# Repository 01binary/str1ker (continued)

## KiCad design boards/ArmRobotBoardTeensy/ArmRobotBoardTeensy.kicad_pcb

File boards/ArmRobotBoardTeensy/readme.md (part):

# Arm Motor Control Board

## Hardware

A Teensy 4.0-based board that controls one 3-degree of freedom (DoF) robot arm with three motors and an end-effector solenoid.

+ The first joint has a digital absolute encoder (AS5045 on SPI bus, see the [custom encoder board](../ArmEncoderBoard/)) and a relative encoder (A/B quadrature interrupt pins), in addition to two limit switches that automatically cut off the "enabled" signal for the first [Mini IBT](https://www.amazon.com/L6201P-Module-H-Bridge-Control-12V-48V/dp/B09N7L9TLB) motor driver.
+ The other two joints have potentiometers and linear actuators with built-in limit switches connected to the remaining two [Mini IBT](https://www.amazon.com/L6201P-Module-H-Bridge-Control-12V-48V/dp/B09N7L9TLB) motor drivers.
+ All three motor drivers have red *enabled* LEDs and blue *activity* LEDs.
+ The solenoid has a blue *activity* LED that indicates when the signal is being sent to [Adafruit MOSFET Driver](https://www.adafruit.com/product/5648).
+ The SPI connection for the absolute encoder has a red *status* LED.
+ [Adafruit INA260](https://www.adafruit.com/product/4226) Voltage and current sensor is attached to the I2C bus. This is used for system identification and PID controller tuning in the lab (not used in production).

The motor drivers control the following motors and actuators:

|Joint|Description|Motor|
|-|-|-|
|Base|Rotates the arm|[DumaDynamics 56RPM Right Angle Gear Motor w/ 13PPR](https://www.robotshop.com/products/duma-dynamics-56rpm-right-angle-gear-motor-w-13ppr-hall-sensor-encoder)
|Shoulder|Raises or lowers the arm|[Firgelli Classic Rod Linear Actuator](https://www.firgelliauto.com/products/linear-actuators?variant=843909131)
|Elbow|Extends or contracts the arm|[Firgelli Bullet Mini Actuator](https://www.firgelliauto.com/products/bullet-series-mini-actuators?variant=20791982342)

The potentiometers that measure shoulder and elbow joint positions are [NP24HS Series](https://p3america.com/np24hs-series/) from P3 America.

## Software

### Controller

+ All three actuators are PID controlled, with encoders normalized to the travel range.
+ Teensy is configured for 12-bit analog conversion.
+ The PID constants for all three actuators are adjustable via [ROS parameters](../../config/arm.yaml) loaded for the ROS Serial node running on the Teensy 4.0 MCU soldered onto this board.

### ROS Interface

+ Target (set-point) positions for all three joints are subscribed to a ROS queue.
+ Velocities of all three joints are subscribed to a ROS queue (velocity overrides position).
+ Trajectory for the whole arm is subscribed to ROS queue (MoveIt Integration with positions, velocities, and torques).
+ Absolute positions of all three joints are published to ROS queue.
+ Status for encoder, motor drivers, voltage, and current are published to ROS queue with lesser frequency.

## Pin Mapping

This board is essentially a shield, exposing convenient, labeled locking connectors for all of the devices, and indicating PWM enabled/activity with LEDs.

|Pin              |Net        |Description
|-----------------|-----------|-------------------
|3V3              |`+3.3V`    |Power
|GND              |`GND`      |Ground
|SPI CS   (`D10`) |`CS`       |Absolute Encoder CS
|SPI SCK  (`D13`) |`SCK`      |Absolute Encoder CK
|SPI MISO (`D12`) |`MISO`     |Absolute Encoder DO
|`D9`             |`SPIS  `   |Absolute Encoder Status LED
|I2C SCL (`D19`)  |`SCL`      |Voltage/Current Sensor SCL
|I2C SDA (`D18`)  |`SDA`      |Voltage/Current Sensor SDA
|`D2`             |`A`        |Quadrature Encoder A
|`D5`             |`B`        |Quadrature Encoder B
|`A0` (`D14`)     |`A0`       |Potentiometer 1
|`A1` (`D15`)     |`A1`       |Potentiometer 2
|`D16`            |`PWM1VT`   |Motor Driver 1 Current Sense
|`D0`             |`PWM1ENSIG`|Motor Driver 1 Enabled
|`D1`             |`RPWM1`    |Motor Driver 1 RPWM
|`D3`             |`LPWM1`    |Motor Driver 1 LPWM
|`D4`             |`PWM2VT`   |Motor Driver 2 Current Sense
|`D6`             |`PWM2EN`   |Motor Driver 2 Enabled
|`D7`             |`RPWM2`    |Motor Driver 2 RPWM
|`D8`             |`LPWM2`    |Motor Driver 2 LPWM
|`D20`            |`PWM3VT`   |Motor Driver 3 Current Sense
|`D21`            |`PWM3EN`   |Motor Driver 3 Enabled
|`D22`            |`RPWM3`    |Motor Driver 3 RPWM
|`D23`            |`LPWM3`    |Motor Driver 3 LPWM
|`D17`            |`SIG`      |Solenoid Driver Signal

## Motor Drivers

There are three external [Mini IBT](https://www.amazon.com/L6201P-Module-H-Bridge-Control-12V-48V/dp/B09N7L9TLB) motor drivers, each with `EN` (enabled), `RPWM` (right PWM velocity), `LPWM` (left PWM velocity) and `VT` (current sense) pins.

Each motor driver has a *status LED* that lights up whenever the driver is enabled (`EN` is `HIGH`).

Each motor driver also has two *activity LEDs* that blink whenever `RPWM` or `LPWM` pins are active. Logic *AND* gates are used along with a 555 timer to blink these activity LEDs whenever a non-zero PWM signal is being sent to these pins.

The 555 timer is configured with two resistors, `10K` and `360K`, for a blink rate of `~2 Hz` (two blinks per second).

The first PWM channel has two normally-open limit switches that cut off the `EN` signal from microcontroller when closed by using a transistor. In this way, even if this PWM channel is enabled by the controller, closing either switch will disable it.

The two linear actuators that control forearm and elbow joints have built-in limit switches but the motor that rotates the arm will happily keep pushing when reaching the limits of its motion, which damages the hardware unnecessarily - these external limit switches solve that problem.

Each motor driver also has a *current sense* pin. These are connected to Teensy ADC pins to read the current of each motor, which is accomplished by placing a `5.1K` resistor to `GND` on current sense lines. The current can be calculated using this formula:

`I = V * 8500 / R` where

+ `I` is the motor current
+ `V` is read voltage from the ADC
+ `R` is the chosen resistor, in this case `5.1K` chosen to produce `3V` on the ADC pin at `5A` (maximum rated) motor current.

Motor drivers are labeled as follows on the schematic:

|Net         |Description
|------------|----------------------------|
|`PWM1EN`    |PWM Channel `1` Enabled
|`RPWM1`     |PWM Channel `1` RPWM
|`LPWM1`     |PWM Channel `1` LPWM
|`PWM1VT`    |PWM Channel `1` Current Sense
|`PWM2EN`    |PWM Channel `2` Enabled
|`RPWM2`     |PWM Channel `2` RPWM
|`LPWM2`     |PWM Channel `2` LPWM
|`PWM2VT`    |PWM Channel `2` Current Sense
|`PWM3EN`    |PWM Channel `3` Enabled
|`RPWM3`     |PWM Channel `3` RPWM
|`LPWM3`     |PWM Channel `3` LPWM
|`PWM3VT`    |PWM Channel `3` Current Sense

## Solenoid

There is one external solenoid connected to [Adafruit MOSFET Driver](https://www.adafruit.com/product/5648) with `VDD` (power), `GND` (ground), and `SIG` (signal) pins. The solenoid driver is enabled when it gets power from Teensy on the `VDD` pin, and gets triggered whenever `SIG` pin is `HIGH`.

The solenoid signal pin has its own activity LED which lights up whenever the solenoid is triggered through the `SIG` pin.

|Net         |Description
|------------|----------------------------|
|`SIG`       |Solenoid Trigger

## Absolute Encoder

An external [absolute encoder board](../ArmEncoderBoard/) is attached to Teensy SPI bus with pins `VDD` (power), `CS` (chip select), `SCK` (SPI clock), `MISO` (SPI input), and `GND` (ground).

When the communication with the encoder is initialized successfully, the controller will set pin `D9` to `HIGH`. This pin is connected to a red encoder status LED.

|Net         |Description
|------------|----------------------------|
|`3V3`       |Absolute Encoder Power
|`GND`       |Absolute Encoder Ground
|`SPIS`      |Absolute Encoder Status LED
|`CS`        |Absolute Encoder SPI Select
|`SCK`       |Absolute Encoder SPI Clock
|`MISO`      |Absolute Encoder SPI Output

## Relative Encoder

An external relative encoder is attached to Teensy interruptable pins `D2` and `D5`. Like the absolute encoder, it is powered through Teensy 3.3V and Ground pins.

This encoder is built into the [DumaDynamics](https://www.robotshop.com/products/duma-dynamics-56rpm-right-angle-gear-motor-w-13ppr-hall-sensor-encoder) motor used to rotate the arm.

|Net         |Description
|------------|----------------------------|
|`3V3`       |Relative Encoder Power
|`GND`       |Relative Encoder Ground
|`A`         |Relative Encoder A Channel
|`B`         |Relative Encoder B Channel

## Potentiometers

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
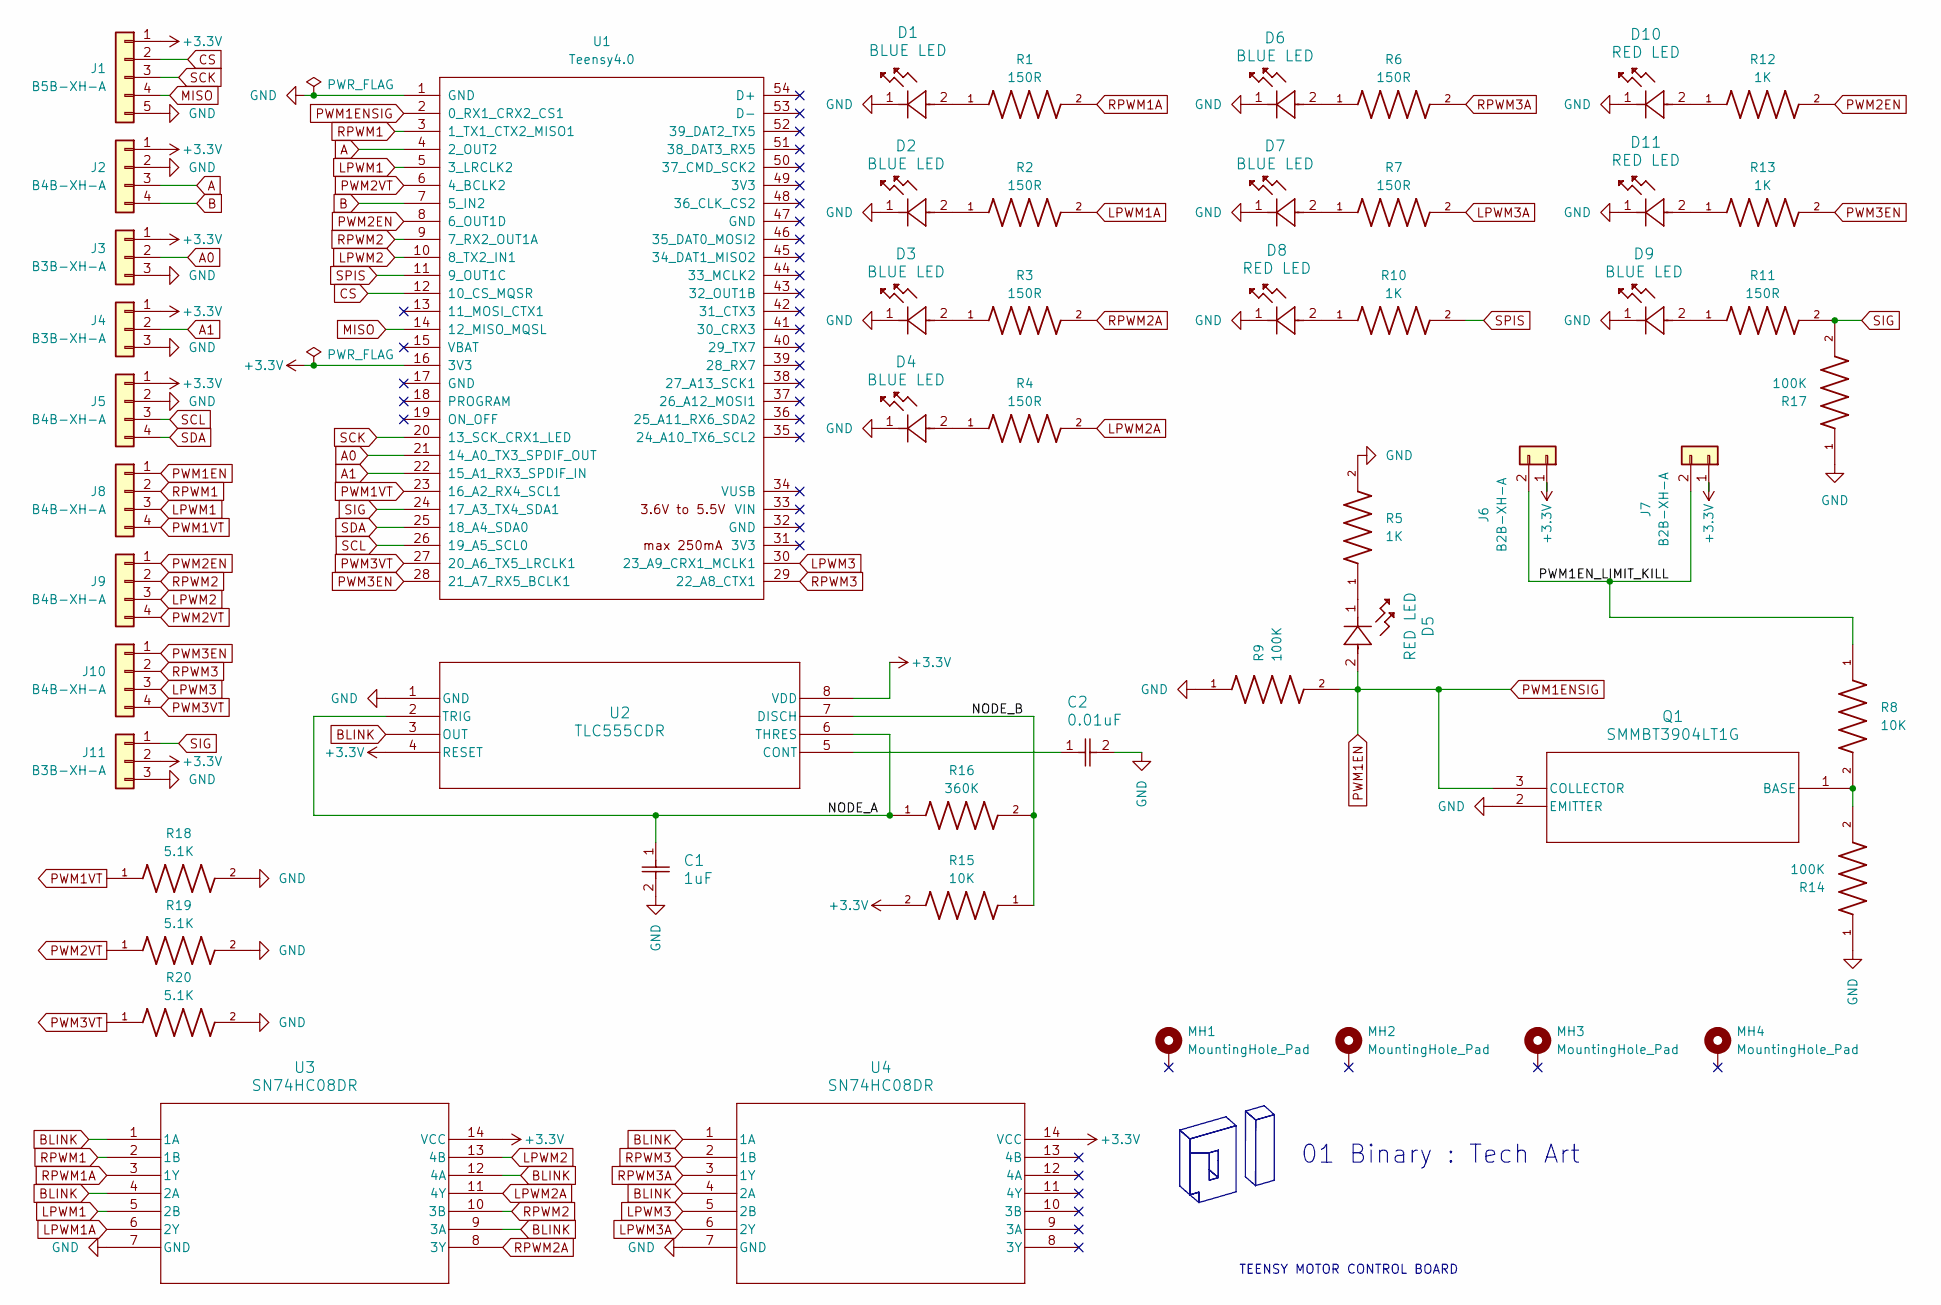
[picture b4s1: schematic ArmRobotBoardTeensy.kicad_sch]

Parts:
C1: 1uF; CC0603JRX7R7BB105; LCSC C519560
C2: 0.01uF; C0402C103J4RACTU; LCSC C2167451
D1, D2, D3, D4, D6, D7, D9: BLUE LED; 150080BS75000_Modified; LCSC C6067133
D5, D8, D10, D11: RED LED; NCD0603R1; LCSC C84263
J1: B5B-XH-A; JST_XH_B5B-XH-A_1x05_P2.50mm_Vertical
J2, J5, J8, J9, J10: B4B-XH-A; JST_XH_B4B-XH-A_1x04_P2.50mm_Vertical
J3, J4, J11: B3B-XH-A; JST_XH_B3B-XH-A_1x03_P2.50mm_Vertical
J6, J7: B2B-XH-A; JST_XH_B2B-XH-A_1x02_P2.50mm_Vertical
MH1, MH2, MH3, MH4: MountingHole_Pad; MountingHole_3.2mm_M3_ISO7380_Pad
Q1: SMMBT3904LT1G; LCSC C84555
R1, R2, R3, R4, R6, R7, R11: 150R; RCG06031K00FKEA; LCSC C114608
R5, R10, R12, R13: 1K; RCG06031K00FKEA; LCSC C4264491
R8, R15: 10K; CRCW060310K0FKEA; LCSC C844918
R9, R14, R17: 100K; CRCW0603100KFKEA; LCSC C844916
R16: 360K; RC0603FR-07360KL; LCSC C137740
R18, R19, R20: 5.1K; RC0603FR-075K1L; LCSC C105580
U1: Teensy4.0; Teensy40_SMT
U2: TLC555CDR; LCSC C6986
U3, U4: SN74HC08DR; LCSC C337768

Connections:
+3.3V: J1.1, J2.1, J3.1, J4.1, J5.1, J6.1, J7.1, J11.2, R15.2, U1.16 (3V3), U2.4 (RESET), U2.8 (VDD), U3.14 (VCC), U4.14 (VCC)
/NODE_A: C1.1, R16.1, U2.2 (TRIG), U2.6 (THRES)
/NODE_B: R15.1, R16.2, U2.7 (DISCH)
/PWM1EN_LIMIT_KILL: J6.2, J7.2, R8.1
A: J2.3, U1.4 (2_OUT2)
A0: J3.2, U1.21 (14_A0_TX3_SPDIF_OUT)
A1: J4.2, U1.22 (15_A1_RX3_SPDIF_IN)
B: J2.4, U1.7 (5_IN2)
BLINK: U2.3 (OUT), U3.1 (1A), U3.4 (2A), U3.9 (3A), U3.12 (4A), U4.1 (1A), U4.4 (2A)
CS: J1.2, U1.12 (10_CS_MQSR)
GND: C1.2, C2.2, D1.1, D2.1, D3.1, D4.1, D6.1, D7.1, D8.1, D9.1, D10.1, D11.1, J1.5, J2.2, J3.3, J4.3, J5.2, J11.3, Q1.2 (EMITTER), R5.2, R9.1, R14.1, R17.1, R18.2, R19.2, R20.2, U1.1 (GND), U2.1 (GND), U3.7 (GND), U4.7 (GND)
LPWM1: J8.3, U1.5 (3_LRCLK2), U3.5 (2B)
LPWM1A: R2.2, U3.6 (2Y)
LPWM2: J9.3, U1.10 (8_TX2_IN1), U3.13 (4B)
LPWM2A: R4.2, U3.11 (4Y)
LPWM3: J10.3, U1.30 (23_A9_CRX1_MCLK1), U4.5 (2B)
LPWM3A: R7.2, U4.6 (2Y)
MISO: J1.4, U1.14 (12_MISO_MQSL)
unnamed: D1.2, R1.1
unnamed: D2.2, R2.1
unnamed: D3.2, R3.1
unnamed: D4.2, R4.1
unnamed: D5.1, R5.1
unnamed: D6.2, R6.1
unnamed: D7.2, R7.1
unnamed: D8.2, R10.1
unnamed: D9.2, R11.1
unnamed: D10.2, R12.1
unnamed: D11.2, R13.1
unnamed: Q1.1 (BASE), R8.2, R14.2
unnamed: C2.1, U2.5 (CONT)
PWM1EN: D5.2, J8.1, Q1.3 (COLLECTOR), R9.2, U1.2 (0_RX1_CRX2_CS1)
PWM1VT: J8.4, R18.1, U1.23 (16_A2_RX4_SCL1)
PWM2EN: J9.1, R12.2, U1.8 (6_OUT1D)
PWM2VT: J9.4, R19.1, U1.6 (4_BCLK2)
PWM3EN: J10.1, R13.2, U1.28 (21_A7_RX5_BCLK1)
PWM3VT: J10.4, R20.1, U1.27 (20_A6_TX5_LRCLK1)
RPWM1: J8.2, U1.3 (1_TX1_CTX2_MISO1), U3.2 (1B)
RPWM1A: R1.2, U3.3 (1Y)
RPWM2: J9.2, U1.9 (7_RX2_OUT1A), U3.10 (3B)
RPWM2A: R3.2, U3.8 (3Y)
RPWM3: J10.2, U1.29 (22_A8_CTX1), U4.2 (1B)
RPWM3A: R6.2, U4.3 (1Y)
SCK: J1.3, U1.20 (13_SCK_CRX1_LED)
SCL: J5.3, U1.26 (19_A5_SCL0)
SDA: J5.4, U1.25 (18_A4_SDA0)
SIG: J11.1, R11.2, R17.2, U1.24 (17_A3_TX4_SDA1)
SPIS: R10.2, U1.11 (9_OUT1C)

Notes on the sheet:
TEENSY MOTOR CONTROL BOARD
01 Binary : Tech Art

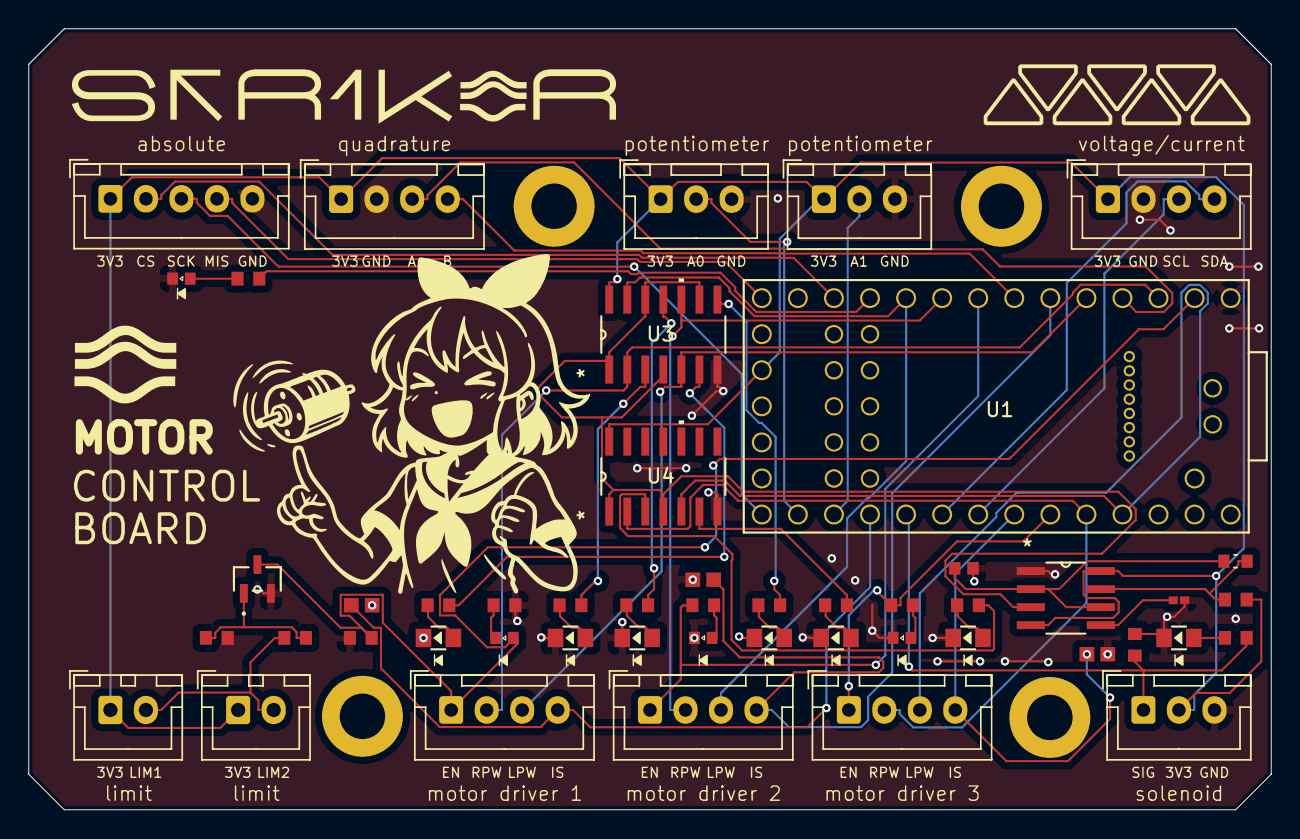
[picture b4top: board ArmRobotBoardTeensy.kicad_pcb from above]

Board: 2 copper layers, 87.5 x 55.0 mm, 53 parts (0 on the bottom side), 48 nets.

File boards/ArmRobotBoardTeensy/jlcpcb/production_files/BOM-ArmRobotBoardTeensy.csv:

Comment,Designator,Footprint,LCSC,Quantity
0.01uF,C2,C0402C103J4RACTU,C2167451,1
100K,"R14,R17,R9",CRCW0603100KFKEA,C844916,3
10K,"R15,R8",CRCW060310K0FKEA,C844918,2
150R,"R1,R11,R2,R3,R4,R6,R7",RCG06031K00FKEA,C114608,7
1uF,C1,CC0603JRX7R7BB105,C519560,1
360K,R16,RC0603FR-07360KL,C137740,1
470R,"R10,R12,R13,R5",RC0603FR-07470RL,C114669,4
BLUE LED,"D1,D2,D3,D4,D6,D7,D9",150080BS75000_Modified,C6067133,7
PINK LED,"D10,D11,D5,D8",LED_XL-2012SURC_XLG,C965812,4
SMMBT3904LT1G,Q1,SMMBT3904LT1G,C84555,1
SN74HC08DR,"U3,U4",SN74HC08DR,C337768,2
TLC555CDR,U2,TLC555CDR,C6986,1

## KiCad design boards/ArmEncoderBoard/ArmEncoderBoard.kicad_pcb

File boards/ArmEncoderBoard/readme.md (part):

# Arm Encoder Board

A custom board that simplifies mounting `AS5045` hall-effect on-axis encoder with 12-bit resolution onto robot joints.

> Ready-made alternatives like [AS5045 Adapter Board](https://www.digikey.com/en/products/detail/ams-osram-usa-inc/as5045-adapterboard/2339623) do exist, but have extra pins not used in this project, and a footprint that makes them hard to mount.

## Power

For `3.3V` operation `VDD5V` and `VDD3V3` are bridged and routed to `VIN` (3.3V). A single `100nF` decoupling capacitor is placed at the bridge (close to the IC) to `GND`.

## Signal

The following is documented in [AS5045 specifications](./doc/AS5045Encoder.pdf):

+ Synchronous Serial Interface ([SSI](https://knowledge.ni.com/KnowledgeArticleDetails?id=kA00Z0000019MgLSAU)) with one-way communication, `MOSI` line not used
+ Compatible with SPI mode 1 (`CPOL` = `0`, `CPHA` = `1`)
+ Transfer begins when `CSn` is `LOW`
+ MSB-first, clocked data output

> The encoder continuously shifts out an 18-bit data frame containing the absolute position and flags in response to clock input without having to request this information - that's what makes its interface *SSI* instead of *SPI*.

In addition to the digital communication interface, AS5045 also exposes these pins:

+ Quadrature `A`, `B` which can take on different values (according to [grey code](https://cool-emerald.blogspot.com/2014/03/reading-rotary-encoder-using.html) specification) as the magnet angle is changing
+ Index `I`, which is signaled when the magnet passes the zero position (typically used to count complete revolutions)
+ Magnet `MagINC`, `MagDEC` pins that indicate magnetic field strength and changing of distance between sensor and magnet (can be used to troubleshoot bad readings or "wobbly" mounting where the magnet changes distance to sensor as it rotates)

## Data Format

The data frame contains 18 bits: 12 data bits, 5 status bits, and 1 parity bit.

| Bit  | Size | Name     | Description
| ---- | ---- | -------- | -------------------------------
| 0–11 | 12   | Position | Angle value (MSB first)
| 12   | 1    | OCF      | Offset Compensation Finished
| 13   | 1    | COF      | CORDIC overflow (invalid angle)
| 14   | 1    | LIN      | Linearity alarm
| 15   | 1    | MagINC   | Magnet too far
| 16   | 1    | MagDEC   | Magnet too close
| 17   | 1    | Parity   | Even parity over previous bits

In practice, it's enough to simply read the first `16` bits using [SPI.transfer16](https://docs.arduino.cc/language-reference/en/functions/communication/SPI/transfer/) function commonly available on Arduino-like microcontrollers such as Teensy.

## Indicators

LEDs are attached to quadrature and index pins as well as magnetic field status pins:

+ The `A` LED blinks when receiving quadrature input (magnet is moving)
+ The `I` LED lights when the encoder is at zero position (magnet is near zero position)
+ The `MagINC` and `MagDEC` LEDs indicate the quality of readings:

|MagINC|MagDEC|Description
|-|-|-
|`0`|`0`|Distance to magnet is not changing, magnetic field OK
|`0`|`1`|Distance to magnet is increasing
|`1`|`0`|Distance to magnet is decreasing
|`1`|`1`|Magnetic field too low (magnet too far from sensor)

The following components are used to enable this:

+ `SN74LVC2G17DBVR` two-channel Schmitt buffer
+ `BAT54WS` Schottky diodes
+ `470K` resistors (transistor base bleed)
+ `47K` resistors (transistor base resistor)
+ `100K` resistors (envelope discharge)
+ `1uF` capacitors (envelope storage)
+ `100nF` capacitor (buffer decoupling)
+ `150R` and `1K` resistors (LED current limit)
+ `MMBT3904` transistors (LED sink drivers)

The `A` quadrature signal from the encoder indicates activity and is connected in the following network:

|Signal|Pin|
|-|-|
|`A`|AS5045 `A` pin going to Schmitt buffer input
|`A_EDGE`|Cleaned edges from Schmitt buffer output
|`A_PULSE`|RC circuit that turns edges into pulses
|`A_ENV`|Envelope circuit that makes pulses last longer
|`A_BLEED`|Envelope bleed
|`A_BASE`|Transistor base input
|`BLUE_CATHODE`|Blue LED cathode
|`BLUE_ANODE`|Blue LED anode

The `I` index signal from the encoder indicates zero position and is connected in the following network:

|Signal|Pin|
|-|-|
|`I`|AS5045 `I` pin going to Schmitt buffer input
|`I_BUF`|Schmitt buffer output
|`I_ENV`|Envelope circuit that makes pulses last longer
|`I_BLEED`|Envelope bleed
|`I_BASE`|Transistor base input
|`BLUE_CATHODE`|Blue LED cathode
|`BLUE_ANODE`|Blue LED anode

### Schmitt Buffer

The Schmitt Trigger Buffer clamps quadrature signals to either `HIGH` or `LOW`, which *cleans the edges* of these signals, making them a *sharp* square wave instead of a *noisy*, approximate, square wave with *soft* edges.

This conditioning is needed because the later stages (a differentiator and an integrator) amplify, and therefore are very sensitive to, noise.

### RC Filter (Differentiator)

The differentiator, implemented by using an RC (*Resistor and Capacitor*) circuit, reacts to *changes* in voltage level.

If the input voltage changes from `HIGH` to `LOW`, the output from the differentiator is `HIGH`, same from `LOW` back to `HIGH`. The differentiator stays `LOW` when the voltage is not changing.

This makes the `A` LED light only when the quadrature signal changes. It's the only way to make an *activity* LED for this kind of signal because a quadrature channel may be left either `HIGH` or `LOW` depending on when the thing being measured stops moving (there is a truth table called the [grey code](https://cool-emerald.blogspot.com/2014/03/reading-rotary-encoder-using.html) that describes the possible states).

### Envelope Generator (Integrator)

Envelope generators modify the transient characteristics of the incoming signal. The one used here acts like an integrator (it accumulates a value over time) by making the signal rise quickly (fast attack) but decay slowly (slow release).

> Fast attack/slow release combination creates "sustain" which enables the LED indicators to stay on long enough to be seen as a "blink" by the human eye after the differentiator detects a change (movement).

Without this part of the circuit, the LEDs would strobe so fast that to a human they would look dimly lit.

### Transistors

Transistors are used to drive LEDs from the power source, using AS5045's A/I pins as on/off switches so they don't drive LEDs directly.

+ Emitter connects to `GND`
+ Collector connects to LED cathode
+ Base connects to `ENV` through `47K` base resistor
+ Base connects to `GND` through `470K` pull-down resistor
+ LED anode connects to `3.3V` through LED resistor (depending on LED color)

### Open-Drain Outputs

The `MagINC` and `MagDEC` pins on AS5045 are open-drain, active-low outputs:

+ When the signals are off (`High-Z`), `10K` resistors are used to pull the lines up to `VIN` bus voltage, making the voltage potential across the corresponding LEDs zero and turning them off (both cathode and anode are bridged to `VIN`).
+ When the signals are on (`LOW`), the LED cathodes get bridged to `GND` through these AS5045 pins (and `1K` current-limiting resistors), while LED anodes remain bridged to `VIN` as before, generating a positive voltage potential and turning the LEDs on.

## Connector

The `JST-XH` connector is designed to accomodate a 5-pin `SSI` interface:

|Position|1|2|3|4|5
|-|-|-|-|-|-|
|Signal|`3V3`|`CS`|`SCK`|`MISO`|`GND`|

This is designed for a simple 5-terminal ribbon with a JST-XH locking connector crimped on.

## Miscellaneous

The following components appear on the board other than the encoder and the connector:

+ `100nF` (`0.1uF`) to `GND` on `VDD`: decoupling capacitor
+ `VDD` and `VDD3V3` bridged on `VIN`: for 3.3V operation
+ `4.7K` to `GND` on `SCK`: clock pull-down
+ `4.7K` to `VIN` on `CS`: chip select pull-up

## Example

```c++
#define CS              10
#define MAG_INC_MASK    0x0001
#define LIN_MASK        0x0002
#define COF_MASK        0x0004
#define OCF_MASK        0x0008
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
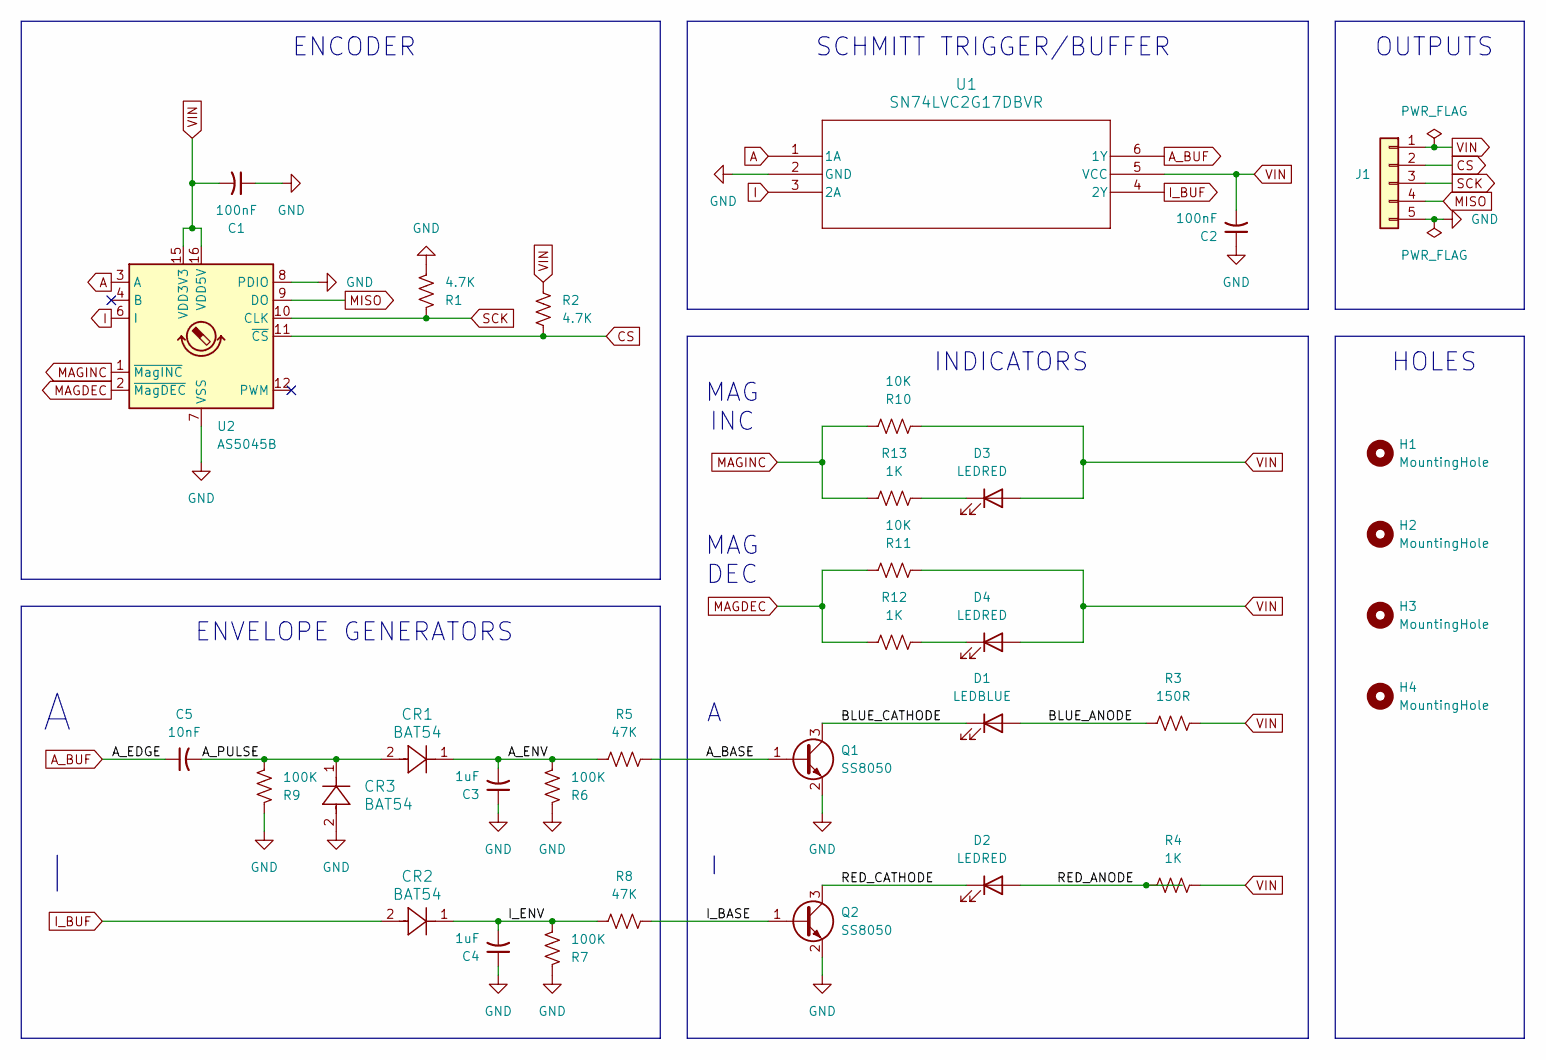
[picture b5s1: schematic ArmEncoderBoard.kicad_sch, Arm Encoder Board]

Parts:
C1, C2: 100nF; CC0603KRX7R9BB104; LCSC C14663
C3, C4: 1uF; CC0603JRX7R7BB105-L; LCSC C519560
C5: 10nF; GRM1885C1H103JA01D; LCSC C85973
CR1, CR2, CR3: BAT54; BAT54WS-7-F; LCSC C124205
D1: LEDBLUE; 150080BS75000_Modified; LCSC C6067133
D2, D3, D4: LEDRED; NCD0603R1; LCSC C84263
H1, H2, H3, H4: MountingHole; MountingHole_3.5mm_Pad
J1: Conn_01x05; JST_XH_B5B-XH-A_1x05_P2.50mm_Vertical
Q1, Q2: SS8050; SOT-23; LCSC C81464
R1, R2: 4.7K; CR0603-FX-4701ELF; LCSC C840629
R3: 150R; RESC1607X60N; LCSC C114608
R4, R12, R13: 1K; RCG06031K00FKEA; LCSC C4264491
R5, R8: 47K; RC0603FR-0747KL; LCSC C105579
R6, R7, R9: 100K; CRCW0603100KFKEA; LCSC C844916
R10, R11: 10K; CRCW060310K0FKEA; LCSC C95204
U1: SN74LVC2G17DBVR; LCSC C10429
U2: AS5045B; SSOP-16_5.3x6.2mm_P0.65mm; LCSC C5375289

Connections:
/A_BASE: Q1.1 (B), R5.1
/A_ENV: C3.2, CR1.1, R5.2, R6.2
/A_PULSE: C5.2, CR1.2, CR3.1, R9.2
/BLUE_ANODE: D1.2 (A), R3.2
/BLUE_CATHODE: D1.1 (K), Q1.3 (C)
/I_BASE: Q2.1 (B), R8.1
/I_ENV: C4.2, CR2.1, R7.2, R8.2
/RED_ANODE: D2.2 (A), R4.2
/RED_CATHODE: D2.1 (K), Q2.3 (C)
A: U1.1 (1A), U2.3 (A)
A_BUF: C5.1, U1.6 (1Y)
CS: J1.2, R2.2, U2.11 (~CS)
GND: C1.1, C2.1, C3.1, C4.1, CR3.2, J1.5, Q1.2 (E), Q2.2 (E), R1.2, R6.1, R7.1, R9.1, U1.2 (GND), U2.7 (VSS), U2.8 (PDIO)
I: U1.3 (2A), U2.6 (I)
I_BUF: CR2.2, U1.4 (2Y)
MAGDEC: R11.2, R12.2, U2.2 (~MagDEC)
MAGINC: R10.2, R13.2, U2.1 (~MagINC)
MISO: J1.4, U2.9 (DO)
unnamed: D3.1 (K), R13.1
unnamed: D4.1 (K), R12.1
SCK: J1.3, R1.1, U2.10 (CLK)
VIN: C1.2, C2.2, D3.2 (A), D4.2 (A), J1.1, R2.1, R3.1, R4.1, R10.1, R11.1, U1.5 (VCC), U2.15 (VDD3V3), U2.16 (VDD5V)

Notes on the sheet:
HOLES
INDICATORS
MAG DEC
ENVELOPE GENERATORS
SCHMITT TRIGGER/BUFFER
ENCODER
MAG INC
OUTPUTS

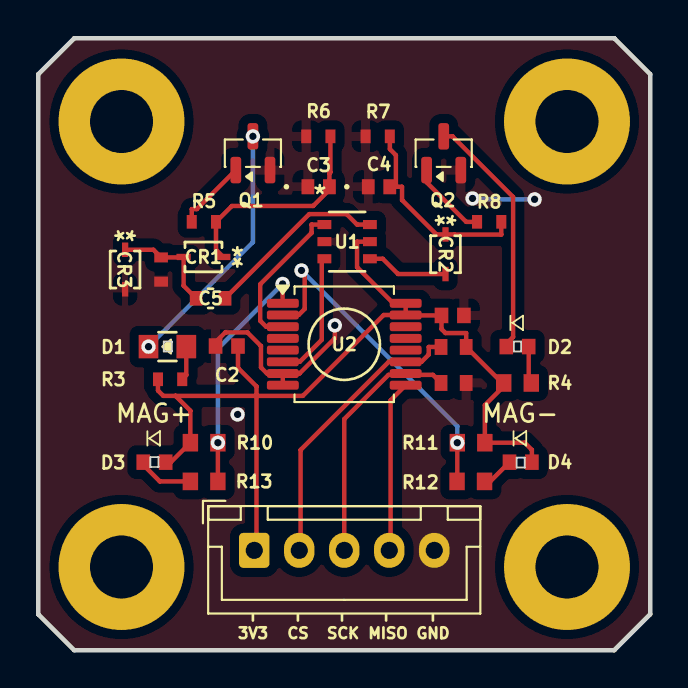
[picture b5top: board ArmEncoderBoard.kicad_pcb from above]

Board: 2 copper layers, 34.0 x 34.0 mm, 34 parts (0 on the bottom side), 22 nets.

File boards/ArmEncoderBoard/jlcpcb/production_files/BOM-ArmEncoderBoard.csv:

Comment,Designator,Footprint,LCSC,Quantity
100K,"R6,R7",CRCW0603100KFKEA,C844916,2
100nF,"C1,C2",CC0603KRX7R9BB104,C14663,2
150R,R3,RESC1607X60N,C114608,1
1K,R4,RCG06031K00FKEA,C4264491,1
1uF,"C3,C4",CC0603JRX7R7BB105-L,C519560,2
4.7K,"R1,R2",CR0603-FX-4701ELF,C840629,2
47K,"R5,R8",RC0603FR-0747KL,C105579,2
AS5045B,U2,SSOP-16_5.3x6.2mm_P0.65mm,C5375289,1
BAT54,"CR1,CR2",BAT54WS-7-F,C124205,2
LEDBLUE,D1,150080BS75000_Modified,C6067133,1
LEDRED,D2,NCD0603R1,C84263,1
SN74LVC2G17DBVR,U1,SN74LVC2G17DBVR,C10429,1
SS8050,"Q1,Q2",SOT-23,C81464,2

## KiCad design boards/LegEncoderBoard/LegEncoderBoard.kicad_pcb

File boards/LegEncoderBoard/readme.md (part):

# Leg Encoder Board

A custom board that simplifies mounting `AS5047P` hall-effect on-axis encoder with 14-bit resolution on robot wheel hubs.

> Ready-made alternatives like [SideView Tech](https://www.amazon.com/AS5047P-Magnetic-Position-Breakout-Compatible/dp/B0DLJ6XDNM) and [AS5047P Adapter Board](https://www.digikey.com/en/products/detail/ams-osram-usa-inc/as5047p-adapterboard/5452344) do exist, but have extra pins not used in this project and a board shape that makes them hard to mount.

## Power

For `3.3V` operation `VDD` and `VDD3V3` are bridged and decoupled to `GND` via `100nF` decoupling capacitor and `10uF` bypass capacitor.

Another `1uF` bulk capacitor is on `VDD3V3` line for additional stabilization.

## Signal

The [AS5047P documentation](./doc/AS5047P.pdf) specifies that `A` and `B` pins output a quadrature signal, and an additional `I` pin outputs index (one pulse per complete revolution). In practice, the index is `HIGH` whenever the encoder is approximately near its zero position.

## Indicators

LEDs are attached to quadrature and index (`A`, `B`, `I`) encoder outputs:
+ The `A` and `B` quadrature LEDs blink when the angle changes
+ The `I` index LED lights when the encoder is approximately over its zero position

The following components are used to enable this:

+ `SN74LVC3G17DCTRE4` triple Schmitt buffer
+ `BAT54WS` Schottky diodes
+ `470K` resistors (transistor base bleed)
+ `47K` resistors (transistor base resistor)
+ `100K` resistors (envelope discharge)
+ `1uF` capacitors (envelope storage)
+ `100nF` capacitor (buffer decoupling)
+ `10nF` capacitor (RC storage)
+ `MMBT3904` transistors (LED sink drivers)

Quadrature signals (`A` and `B`) are connected in the following network:

|Signal|Pin|
|-|-|
|`A`, `B`|AS5047 A, B pins going to Schmitt buffer inputs
|`A_BUF`, `B_BUF`|Schmitt buffer output
|`A_EDGE`, `B_EDGE`|Cleaned edges from Schmitt buffer output
|`A_PULSE`, `B_PULSE`|RC circuit that turns edges into pulses
|`A_ENV`, `B_ENV`|Envelope circuit that makes pulses last longer
|`A_BASE`, `B_BASE`|Transistor base
|`A_LED_CATHODE`, `B_LED_CATHODE`|LED cathode
|`A_LED_ANODE`, `B_LED_ANODE`|LED anode

Index signal (`I`) is connected in the following network:

|Signal|Pin|
|-|-|
|`I`|AS5047 I pin to Schmitt buffer input
|`I_BUF`|Schmitt buffer output
|`I_ENV`|Envelope circuit that makes pulses last longer
|`I_BASE`|Transistor base
|`I_LED_CATHODE`|LED cathode
|`I_LED_ANODE`|LED anode

Both Quadrature and Index signals use an integrator circuit to make fast changes visible. Quadrature signals add a differentiator before the integrator to make the lights react only to changes in the quadrature signal, rather than the actual signal.

### Schmitt Buffer

The Schmitt Trigger Buffer clamps quadrature signals to either `HIGH` or `LOW`, which *cleans the edges* of these signals, making them a *sharp* square wave instead of a *noisy*, approximate, square wave with *soft* edges.

This conditioning is needed because the later stages (a differentiator and an integrator) amplify, and therefore are very sensitive to, noise.

### RC Filter (Differentiator)

The differentiator, implemented by using an RC (*Resistor and Capacitor*) circuit, reacts to *changes* in voltage level.

If the input voltage changes from `HIGH` to `LOW`, the output from the differentiator is `HIGH`, same from `LOW` back to `HIGH`. The differentiator stays `LOW` when the voltage is not changing.

This makes the LEDs light only when the quadrature signal changes. It's the only way to make an *activity* LED for this kind of signal because quadrature `A` and `B` channels may be left either `HIGH` or `LOW` depending on when the thing being measured stops moving (there is a truth table called the [grey code](https://cool-emerald.blogspot.com/2014/03/reading-rotary-encoder-using.html) that describes the possible states).

### Envelope Generator (Integrator)

Envelope generators modify the transient characteristics of the incoming signal. The one used here acts like an integrator (it accumulates a value over time) by making the signal rise quickly (fast attack) but decay slowly (slow release).

> Fast attack/slow release combination creates "sustain" which enables the LED indicators to stay on long enough to be seen as a "blink" by the human eye after the differentiator detects a change (movement).

Without this part of the circuit, the LEDs would strobe so fast that to a human they would look dimly lit.

### Transistors

Transistors are used to drive LEDs from the power source, using AS5047's A/B/I pins as on/off switches so they don't drive LEDs directly.

+ Emitter connects to `GND`
+ Collector connects to `LED_CATHODE`
+ Base connects to `ENV` through `47K` base resistor (transitor base is a diode much like an LED, and needs a current-limiting resistor, otherwise Teensy will dump all its available current into the gate, which adds up quickly)
+ Base connects to `GND` through `470K` pull-down resistor (this helps ensure the gate stays closed when connected to nothing, such as during boot)

### Indicators

+ LED anode (`LED_CATHODE`) connects to `3.3V` through LED resistor (depending on LED color)
+ LED cathode (`LED_ANODE`) connects to transistor collector

## Connector

The board uses an IDC connector with 2 rows of 4 pins. This enables twisting each of the four signal wires with ground for better interference rejection.

Conveniently, [CAT5E](https://www.amazon.com/dp/B00KWS6TWS) cables have this precise layout: 8 wires, 4 of them signals, 4 of them grounds, each signal twisted with its ground along the entire length of the cable.

All that remains is cutting off the `RJ45` connectors and crimping on [Molex 0022552082](https://www.digikey.com/en/products/detail/molex/0022552082/313629) / [Molex 0016020086](https://www.digikey.com/en/products/detail/molex/0016020086/467788) to make female locking connectors that fit into IDC male receptacles.

|Column|1|2|3|4|
|-|-|-|-|-|
|Row 1|`3V3`|`GND`|`A`|`GND`|
|Row 2|`B`|`GND`|`I`|`GND`|

## Example

The following can be used to initialize the encoder on [Teensy 4.0](https://www.sparkfun.com/teensy-4-0.html) and read quadrature input:

```c++
#include <Arduino.h>
#include <Encoder.h>

#define PIN_A 2
#define PIN_B 3
#define PIN_I 4

Encoder encoder(PIN_A, PIN_B);
volatile uint32_t revolutions = 0;

void indexInterrupt()
{
  revolutions++;
}

void setup()
{
  Serial.begin(115200);
  while (!Serial && millis() < 2000);

  pinMode(PIN_A, INPUT);
  pinMode(PIN_B, INPUT);
  pinMode(PIN_I, INPUT);

  attachInterrupt(
    digitalPinToInterrupt(PIN_I),
    indexInterrupt,
    RISING
  );

  encoder.write(0);
}

void loop()
{
  int32_t counts = encoder.read();

  Serial.print("counts ");
  Serial.print(counts);
  Serial.print("revolutions ");
  Serial.println(revolutions);

  delay(10);
}
```

## Bill of Materials

|Component|Description|
|-|-|
|[AS5047P-ATST](https://www.digikey.com/en/products/detail/ams-osram-usa-inc/as5047p-atst-tssop14-lf-t-rdp/5288535)|Encoder|
|[CC0603KRX7R9BB104](https://www.digikey.com/en/products/detail/yageo/cc0603krx7r9bb104/2103082)|`100nF` Decoupling Capacitor|
|[GRM1885C1H103JA01D](https://www.digikey.com/en/models/4421555)|`10nF` Bypass Capacitor|
|[CC0603JRX7R7BB105](https://www.digikey.com/en/products/detail/yageo/CC0603JRX7R7BB105/7164369)|`1uF` Bulk Capacitor, Envelope Capacitor|
|[150080BS75000](https://www.digikey.com/en/products/detail/w%C3%BCrth-elektronik/)|Blue LED for A and B channels|
|[NCD0603R1](https://www.lcsc.com/product-detail/C84263.html?s_z=s_C84263)|Red LED for I channel|
|[RC0603FR-07470KL](https://www.digikey.com/en/products/detail/yageo/rc0603fr-07470kl/727257)|`470K` Bleed Resistor|
|[RCG06031K00FKEA](https://www.digikey.com/en/products/detail/vishay-dale/rcg06031k00fkea/4172389)|`1K` Resistor (Red LED)|
|[RC0603FR-0747KL](https://www.digikey.com/en/products/detail/yageo/RC0603FR-0747KL/730200)|`47K` Transistor Base Resistor|
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
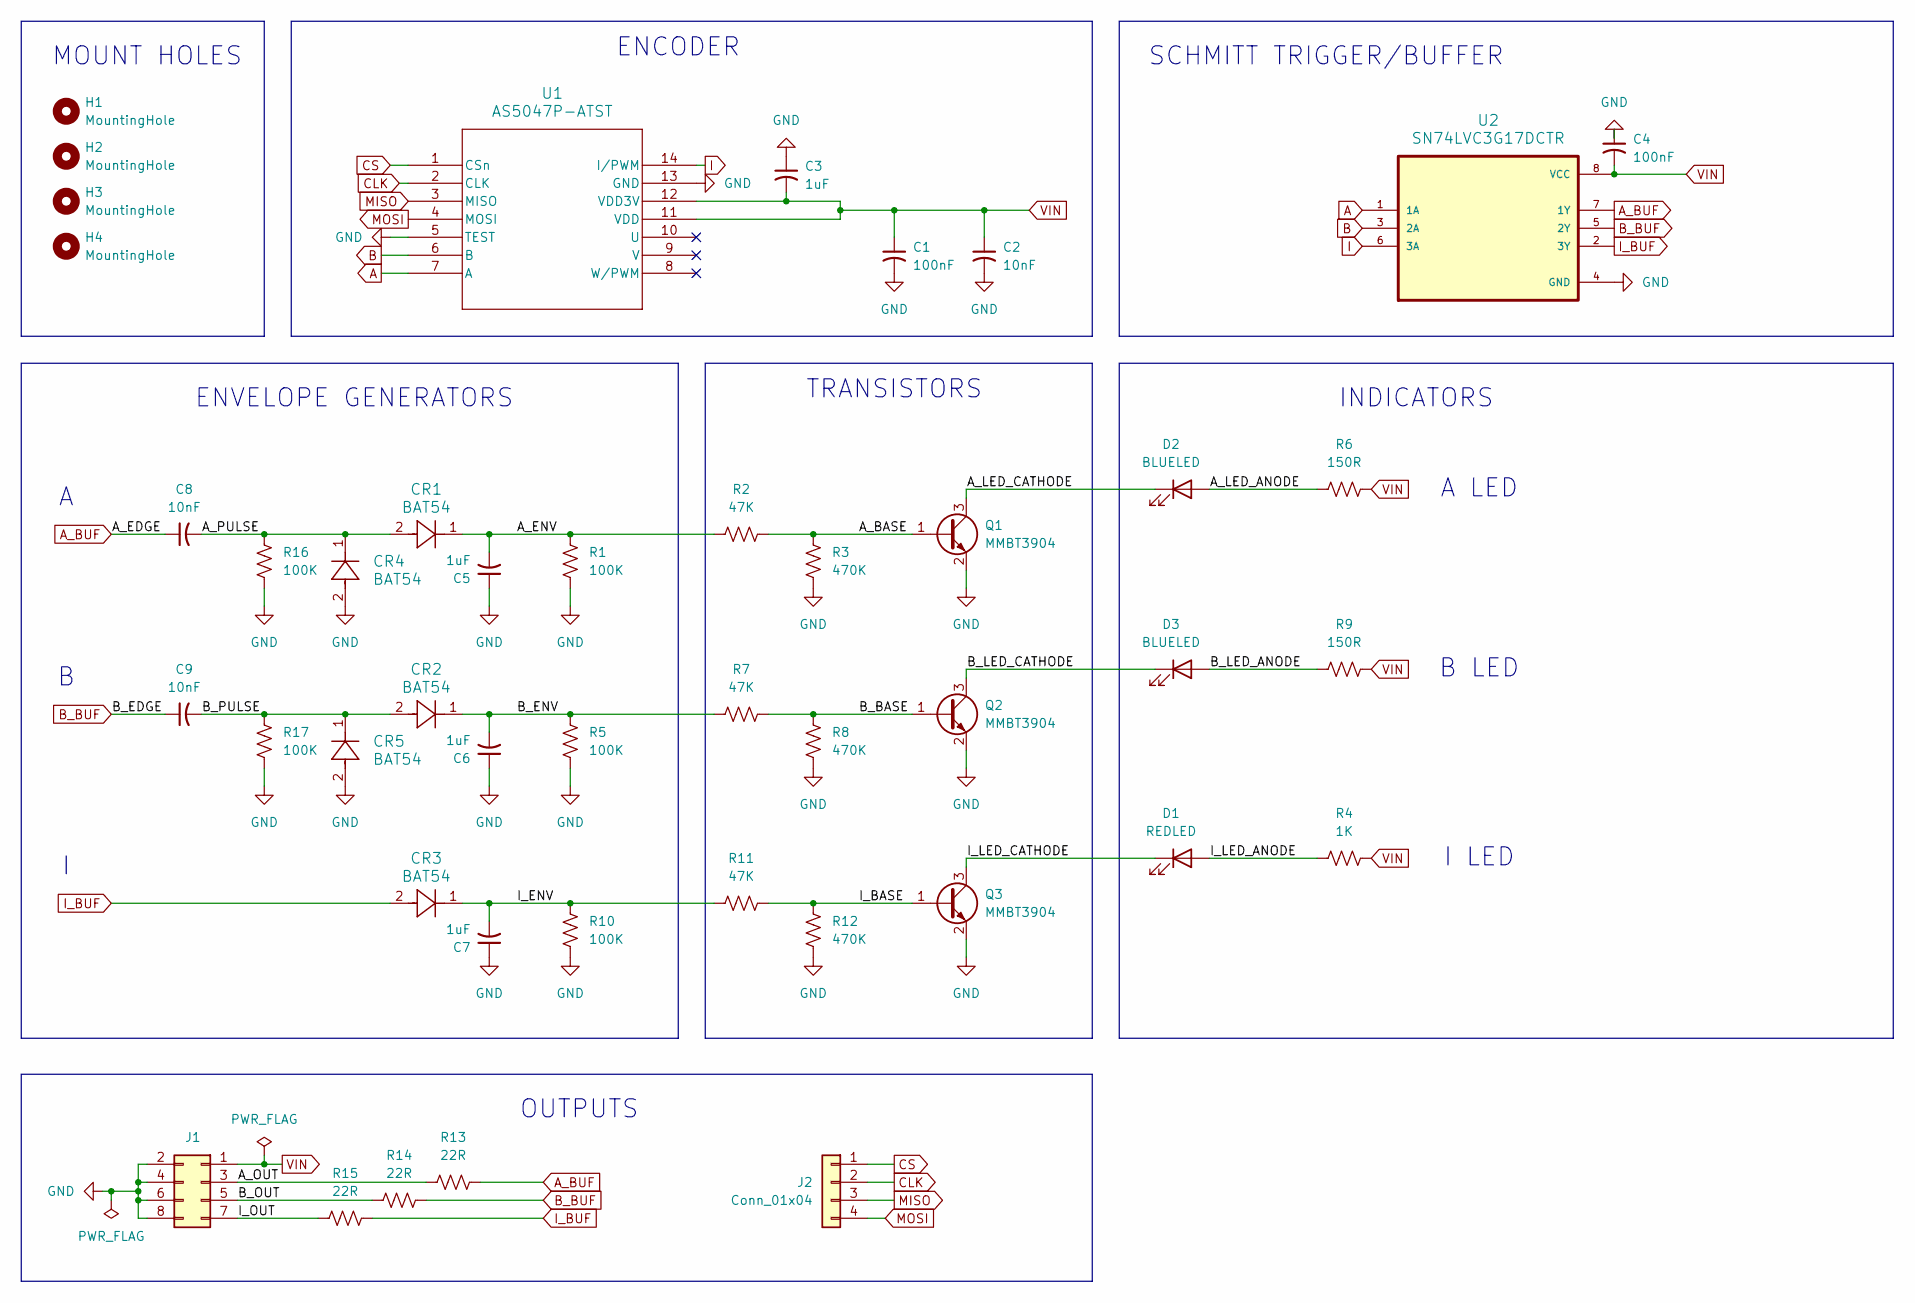
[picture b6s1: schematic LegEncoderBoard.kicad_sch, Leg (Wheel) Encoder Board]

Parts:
C1, C4: 100nF; CC0603KRX7R9BB104; LCSC C14663
C2, C8, C9: 10nF; GRM1885C1H103JA01D; LCSC C85973
C3, C5, C6, C7: 1uF; CC0603JRX7R7BB105; LCSC C519560
CR1, CR2, CR3, CR4, CR5: BAT54; BAT54WS-7-F; LCSC C124205
D1: REDLED; NCD0603R1; LCSC C114608
D2, D3: BLUELED; 150080BS75000_Modified; LCSC C6067133
H1, H2, H3, H4: MountingHole; MountingHole_2.5mm_Pad
J1: Conn_01x05; IDC-Header_2x04_P2.54mm_Vertical
J2: Conn_01x04; JST_XH_B4B-XH-A_1x04_P2.50mm_Vertical
Q1, Q2, Q3: MMBT3904; MMBT3904LT1G; LCSC C81464
R1, R5, R10, R16, R17: 100K; CRCW0603100KFKEA; LCSC C844916
R2, R7, R11: 47K; RC0603FR-0747KL; LCSC C105579
R3, R8, R12: 470K; RC0603FR-07470KL; LCSC C114622
R4: 1K; RCG06031K00FKEA; LCSC C4264491
R6, R9: 150R; RESC1607X60N; LCSC C114608
R13, R14, R15: 22R; RC0603FR-0722RL; LCSC C107701
U1: AS5047P-ATST; AS5047P-ASST; LCSC C962063
U2: SN74LVC3G17DCTR; PARTREV F; LCSC C18213

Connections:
/A_BASE: Q1.1 (B), R2.2, R3.1
/A_ENV: C5.2, CR1.1, R1.1, R2.1
/A_LED_ANODE: D2.2 (A), R6.2
/A_LED_CATHODE: D2.1 (K), Q1.3 (C)
/A_OUT: J1.3, R13.1
/A_PULSE: C8.2, CR1.2, CR4.1, R16.1
/B_BASE: Q2.1 (B), R7.2, R8.1
/B_ENV: C6.2, CR2.1, R5.1, R7.1
/B_LED_ANODE: D3.2 (A), R9.2
/B_LED_CATHODE: D3.1 (K), Q2.3 (C)
/B_OUT: J1.5, R14.1
/B_PULSE: C9.2, CR2.2, CR5.1, R17.1
/I_BASE: Q3.1 (B), R11.2, R12.1
/I_ENV: C7.2, CR3.1, R10.1, R11.1
/I_LED_ANODE: D1.2 (A), R4.2
/I_LED_CATHODE: D1.1 (K), Q3.3 (C)
/I_OUT: J1.7, R15.1
A: U1.7 (A), U2.1 (1A)
A_BUF: C8.1, R13.2, U2.7 (1Y)
B: U1.6 (B), U2.3 (2A)
B_BUF: C9.1, R14.2, U2.5 (2Y)
CLK: J2.2, U1.2 (CLK)
CS: J2.1, U1.1 (CSn)
GND: C1.2, C2.2, C3.1, C4.1, C5.1, C6.1, C7.1, CR4.2, CR5.2, J1.2, J1.4, J1.6, J1.8, Q1.2 (E), Q2.2 (E), Q3.2 (E), R1.2, R3.2, R5.2, R8.2, R10.2, R12.2, R16.2, R17.2, U1.5 (TEST), U1.13 (GND), U2.4 (GND)
I: U1.14 (I/PWM), U2.6 (3A)
I_BUF: CR3.2, R15.2, U2.2 (3Y)
MISO: J2.3, U1.3 (MISO)
MOSI: J2.4, U1.4 (MOSI)
VIN: C1.1, C2.1, C3.2, C4.2, J1.1, R4.1, R6.1, R9.1, U1.11 (VDD), U1.12 (VDD3V), U2.8 (VCC)

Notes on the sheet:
ENVELOPE GENERATORS
ENCODER
I LED
B LED
INDICATORS
OUTPUTS
A LED
MOUNT HOLES
TRANSISTORS
SCHMITT TRIGGER/BUFFER

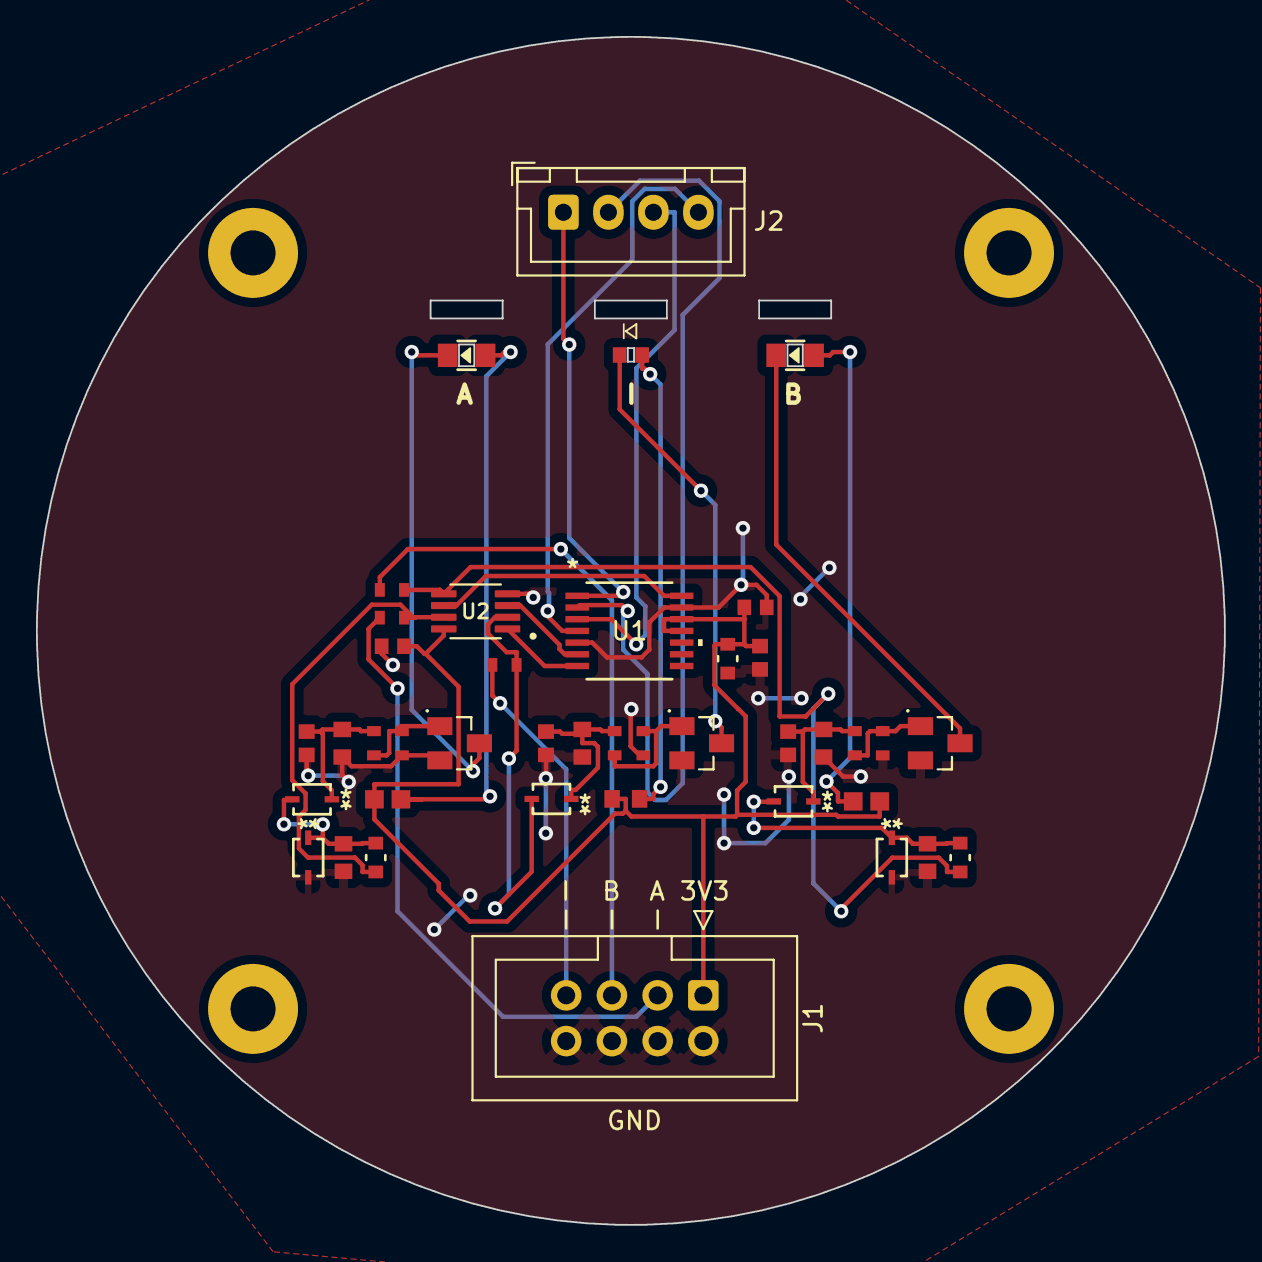
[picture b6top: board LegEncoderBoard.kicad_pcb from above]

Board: 2 copper layers, 66.0 x 66.0 mm, 45 parts (0 on the bottom side), 29 nets.

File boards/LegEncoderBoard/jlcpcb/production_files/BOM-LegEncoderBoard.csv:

Comment,Designator,Footprint,LCSC,Quantity
100K,"R1,R10,R16,R17,R5",CRCW0603100KFKEA,C844916,5
100nF,"C1,C4",CC0603KRX7R9BB104,C14663,2
10nF,"C2,C8,C9",GRM1885C1H103JA01D,C85973,3
150R,"R6,R9",RESC1607X60N,C114608,2
1K,R4,RCG06031K00FKEA,C4264491,1
1uF,"C3,C5,C6,C7",CC0603JRX7R7BB105,C519560,4
22R,"R13,R14,R15",RC0603FR-0722RL,C107701,3
470K,"R12,R3,R8",RC0603FR-07470KL,C114622,3
47K,"R11,R2,R7",RC0603FR-0747KL,C105579,3
AS5047P-ATST,U1,AS5047P-ASST,C962063,1
BAT54,"CR1,CR2,CR3,CR4,CR5",BAT54WS-7-F,C124205,5
BLUELED,"D2,D3",150080BS75000_Modified,C6067133,2
MMBT3904,"Q1,Q2,Q3",MMBT3904LT1G,C81464,3
REDLED,D1,NCD0603R1,C84263,1
SN74LVC3G17DCTR,U2,SN74LVC3G17DCTR,C18213,1
